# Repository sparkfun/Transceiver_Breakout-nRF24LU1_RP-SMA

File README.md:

SparkFun Transceiver Breakout - nRF24LU1+ (RP-SMA)
========================================

[*SparkFun Transceiver Breakout - nRF24LU1+ (RP-SMA) (WRL-09034)*](https://www.sparkfun.com/products/9034)

This is a breakout board for Nordic’s nRF24LU1+ system-on-chip wireless transceiver. 
The nRF24LU1+ features a fully integrated USB 2.0 compliant device controller, which allows for a very compact wireless USB dongle. The nRF24LU1+ is compatible with our nRF24L01+ 2.4GHz RF transceivers as well. 
Additional features include an 8-bit application microcontroller, 32 kB flash memory, 6 GPIO pins, SPI and UART support, and up to 2Mbps on air data rates.

Repository Contents
-------------------

* **/Hardware** - Eagle design files (.brd, .sch)
* **/Production** - Production panel files (.brd)

Documentation
--------------
* **[SparkFun Fritzing repo](https://github.com/sparkfun/Fritzing_Parts)** - Fritzing diagrams for SparkFun products.
* **[SparkFun 3D Model repo](https://github.com/sparkfun/3D_Models)** - 3D models of SparkFun products. 

License Information
-------------------
This product is _**open source**_! 

The **hardware** is released under [Creative Commons ShareAlike 4.0 International](https://creativecommons.org/licenses/by-sa/4.0/).

Please use, reuse, and modify these files as you see fit. Please maintain attribution to SparkFun Electronics and release anything derivative under the same license.

Distributed as-is; no warranty is given.

- Your friends at SparkFun.

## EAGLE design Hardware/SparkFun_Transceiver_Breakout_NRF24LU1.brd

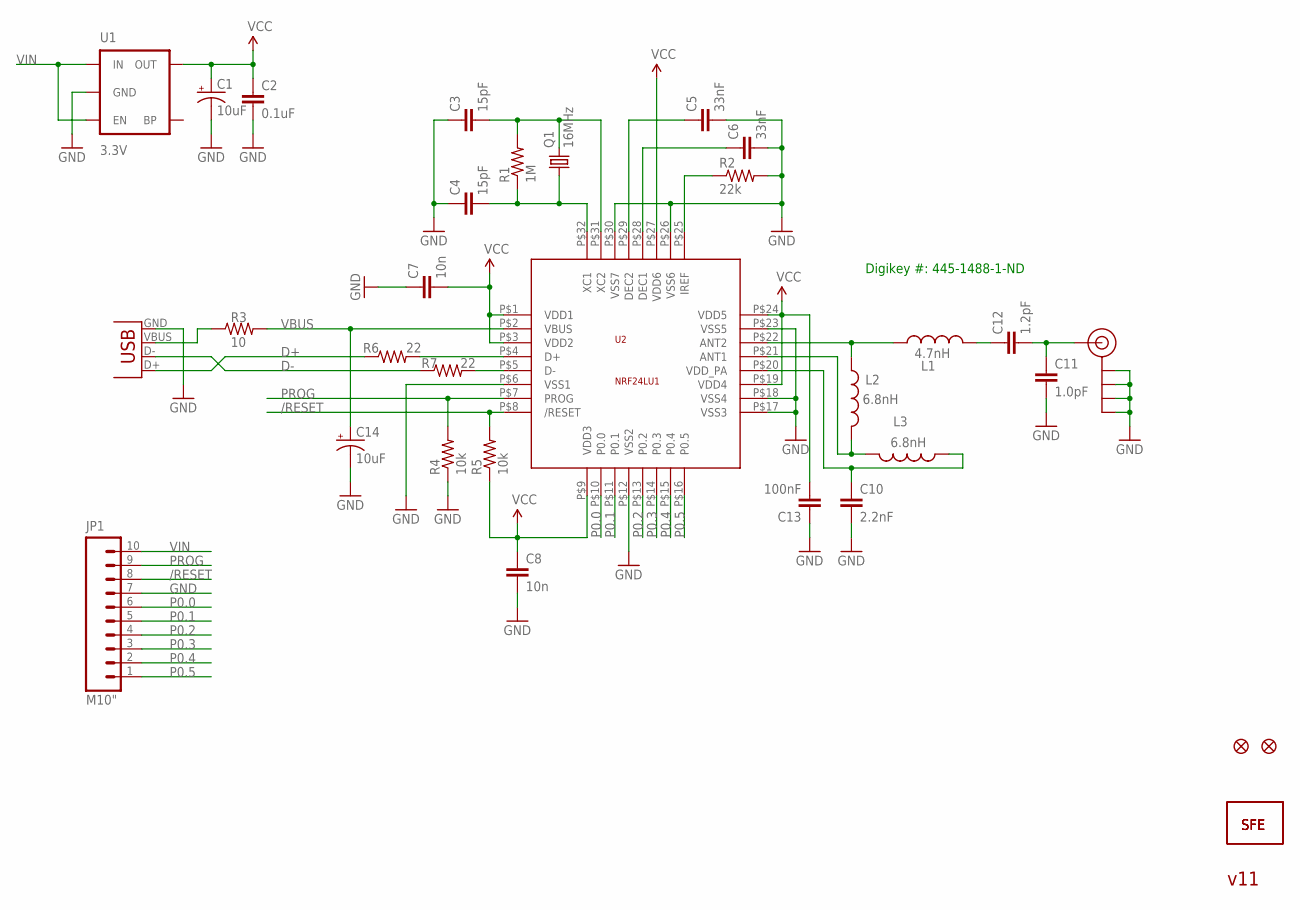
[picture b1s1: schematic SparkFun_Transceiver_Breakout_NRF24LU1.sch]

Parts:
C1, C14: 10uF; EIA3216
C2: 0.1uF; 0402-CAP
C3, C4: 15pF; 0402-CAP
C5, C6: 33nF; 0402-CAP
C7, C8: 10n; 0402-CAP
C10: 2.2nF; 0402-CAP
C11: 1.0pF; 0402-CAP
C12: 1.2pF; 0402-CAP
C13: 100nF; 0402-CAP
J$1: SMA_EDGE; SMA-EDGE
JP1: M10"; 1X10
JP2: LOGO-SFENEW; SFE-NEW-WEBLOGO
L1: 4.7nH; C0402
L2, L3: 6.8nH; C0402
Q1: 16MHz; CRYSTAL-SMD-5X3
R1: 1M; 0402-RES
R2: 22k; 0402-RES
R3: 10; 1206
R4, R5: 10k; 0402-RES
R6, R7: 22; 0402-RES
U1: 3.3V; SOT23-5
U2: NRF24LU1; QFN-32
U$12, U$13: FIDUCIAL1X2; FIDUCIAL-1X2
U$14: LOGO-SFESK; SFE-LOGO-FLAME
X1: USBSMD; USB-MINIB

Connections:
/RESET: JP1.8, R5.2, U2.P$8 (/RESET)
D+: R6.1, X1.D+
D-: R7.1, X1.D-
GND: C1.C (-), C2.2, C3.1, C4.1, C5.2, C6.2, C7.1, C8.2, C10.2, C11.2, C13.1, C14.C (-), J$1.GND@0 (GND), J$1.GND@1 (GND), J$1.GND@2 (GND), J$1.GND@3 (GND), JP1.7, R2.2, R4.1, U1.2 (GND), U2.P$6 (VSS1), U2.P$12 (VSS2), U2.P$17 (VSS3), U2.P$18 (VSS4), U2.P$23 (VSS5), U2.P$26 (VSS6), U2.P$30 (VSS7), X1.GND
unnamed: C3.2, Q1.3 (2), R1.2, U2.P$31 (XC2)
unnamed: C4.2, Q1.1, R1.1, U2.P$32 (XC1)
unnamed: L1.1, L2.1, U2.P$22 (ANT2)
unnamed: C5.1, U2.P$29 (DEC2)
unnamed: R6.2, U2.P$4 (D+)
unnamed: R3.1, X1.VBUS
unnamed: R7.2, U2.P$5 (D-)
unnamed: C6.1, U2.P$28 (DEC1)
unnamed: R2.1, U2.P$25 (IREF)
unnamed: C12.1, L1.2
unnamed: C11.1, C12.2, J$1.SIG (SIGNAL)
unnamed: L2.2, L3.2, U2.P$21 (ANT1)
unnamed: C10.1, L3.1, U2.P$20 (VDD_PA)
P0.0: JP1.6, U2.P$10 (P0.0)
P0.1: JP1.5, U2.P$11 (P0.1)
P0.2: JP1.4, U2.P$13 (P0.2)
P0.3: JP1.3, U2.P$14 (P0.3)
P0.4: JP1.2, U2.P$15 (P0.4)
P0.5: JP1.1, U2.P$16 (P0.5)
PROG: JP1.9, R4.2, U2.P$7 (PROG)
VBUS: C14.A (+), R3.2, U2.P$2 (VBUS)
VCC: C1.A (+), C2.1, C7.2, C8.1, C13.2, R5.1, U1.5 (OUT), U2.P$1 (VDD1), U2.P$3 (VDD2), U2.P$9 (VDD3), U2.P$19 (VDD4), U2.P$24 (VDD5), U2.P$27 (VDD6)
VIN: JP1.10, U1.1 (IN), U1.3 (EN)

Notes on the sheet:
Digikey #: 445-1488-1-ND
v11

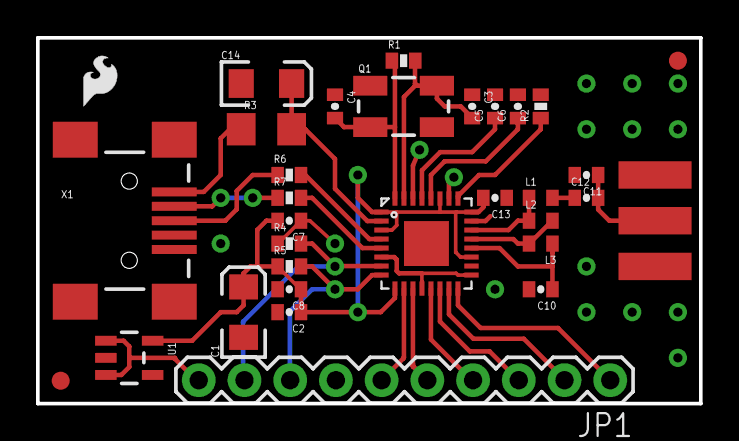
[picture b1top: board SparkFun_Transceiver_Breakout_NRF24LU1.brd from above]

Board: 2 copper layers, 36.8 x 20.3 mm, 33 parts (1 on the bottom side), 27 nets.

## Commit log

2015-05-11 Adding hardware
